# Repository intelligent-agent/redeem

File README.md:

```
     _/_/_/                    _/                                     
    _/    _/    _/_/      _/_/_/    _/_/      _/_/    _/_/_/  _/_/    
   _/_/_/    _/_/_/_/  _/    _/  _/_/_/_/  _/_/_/_/  _/    _/    _/   
  _/    _/  _/        _/    _/  _/        _/        _/    _/    _/    
 _/    _/    _/_/_/    _/_/_/    _/_/_/    _/_/_/  _/    _/    _/     
```

Replicape is an attachment for BeagleBone to control control 3D printers and CNC machines, such as routers, lathes and mills.

Redeem is its firmware; it accepts g-codes and translates them into coordinates for your device.

## Software features

- Acceleration with corner speed prediction
- Printer settings loaded from files
- Controllable via OctoPrint, ethernet, USB or MagnaScreen
- Written in python for extensibility
- Optimized for BeagleBone's secondary processing units
- Extendable plugin architecture

## Documentation

[http://wiki.thing-printer.com/](Intelligent-Agent Wiki)

## Installation options

### BeagleBone image

Umikaze (based on Ubuntu 18.04.2 LTS)

### Source install

**WARNING**: The current `master` branch is considered stable, though not yet released while we integrate a few more features to release 2.2.1.
As such, please note that as of this latest change to the master branch, you should be building Redeem off a platform similar to that built by the [https://github.com/intelligent-agent/Umikaze](Umikaze) 
[https://github.com/intelligent-agent/Umikaze/blob/master/Packages/install_redeem](Redeem build script).

The build script will not run as a standalone, however it does include all dependency installations and virtual environment setup, as well as inclusion of the systemd service integration.

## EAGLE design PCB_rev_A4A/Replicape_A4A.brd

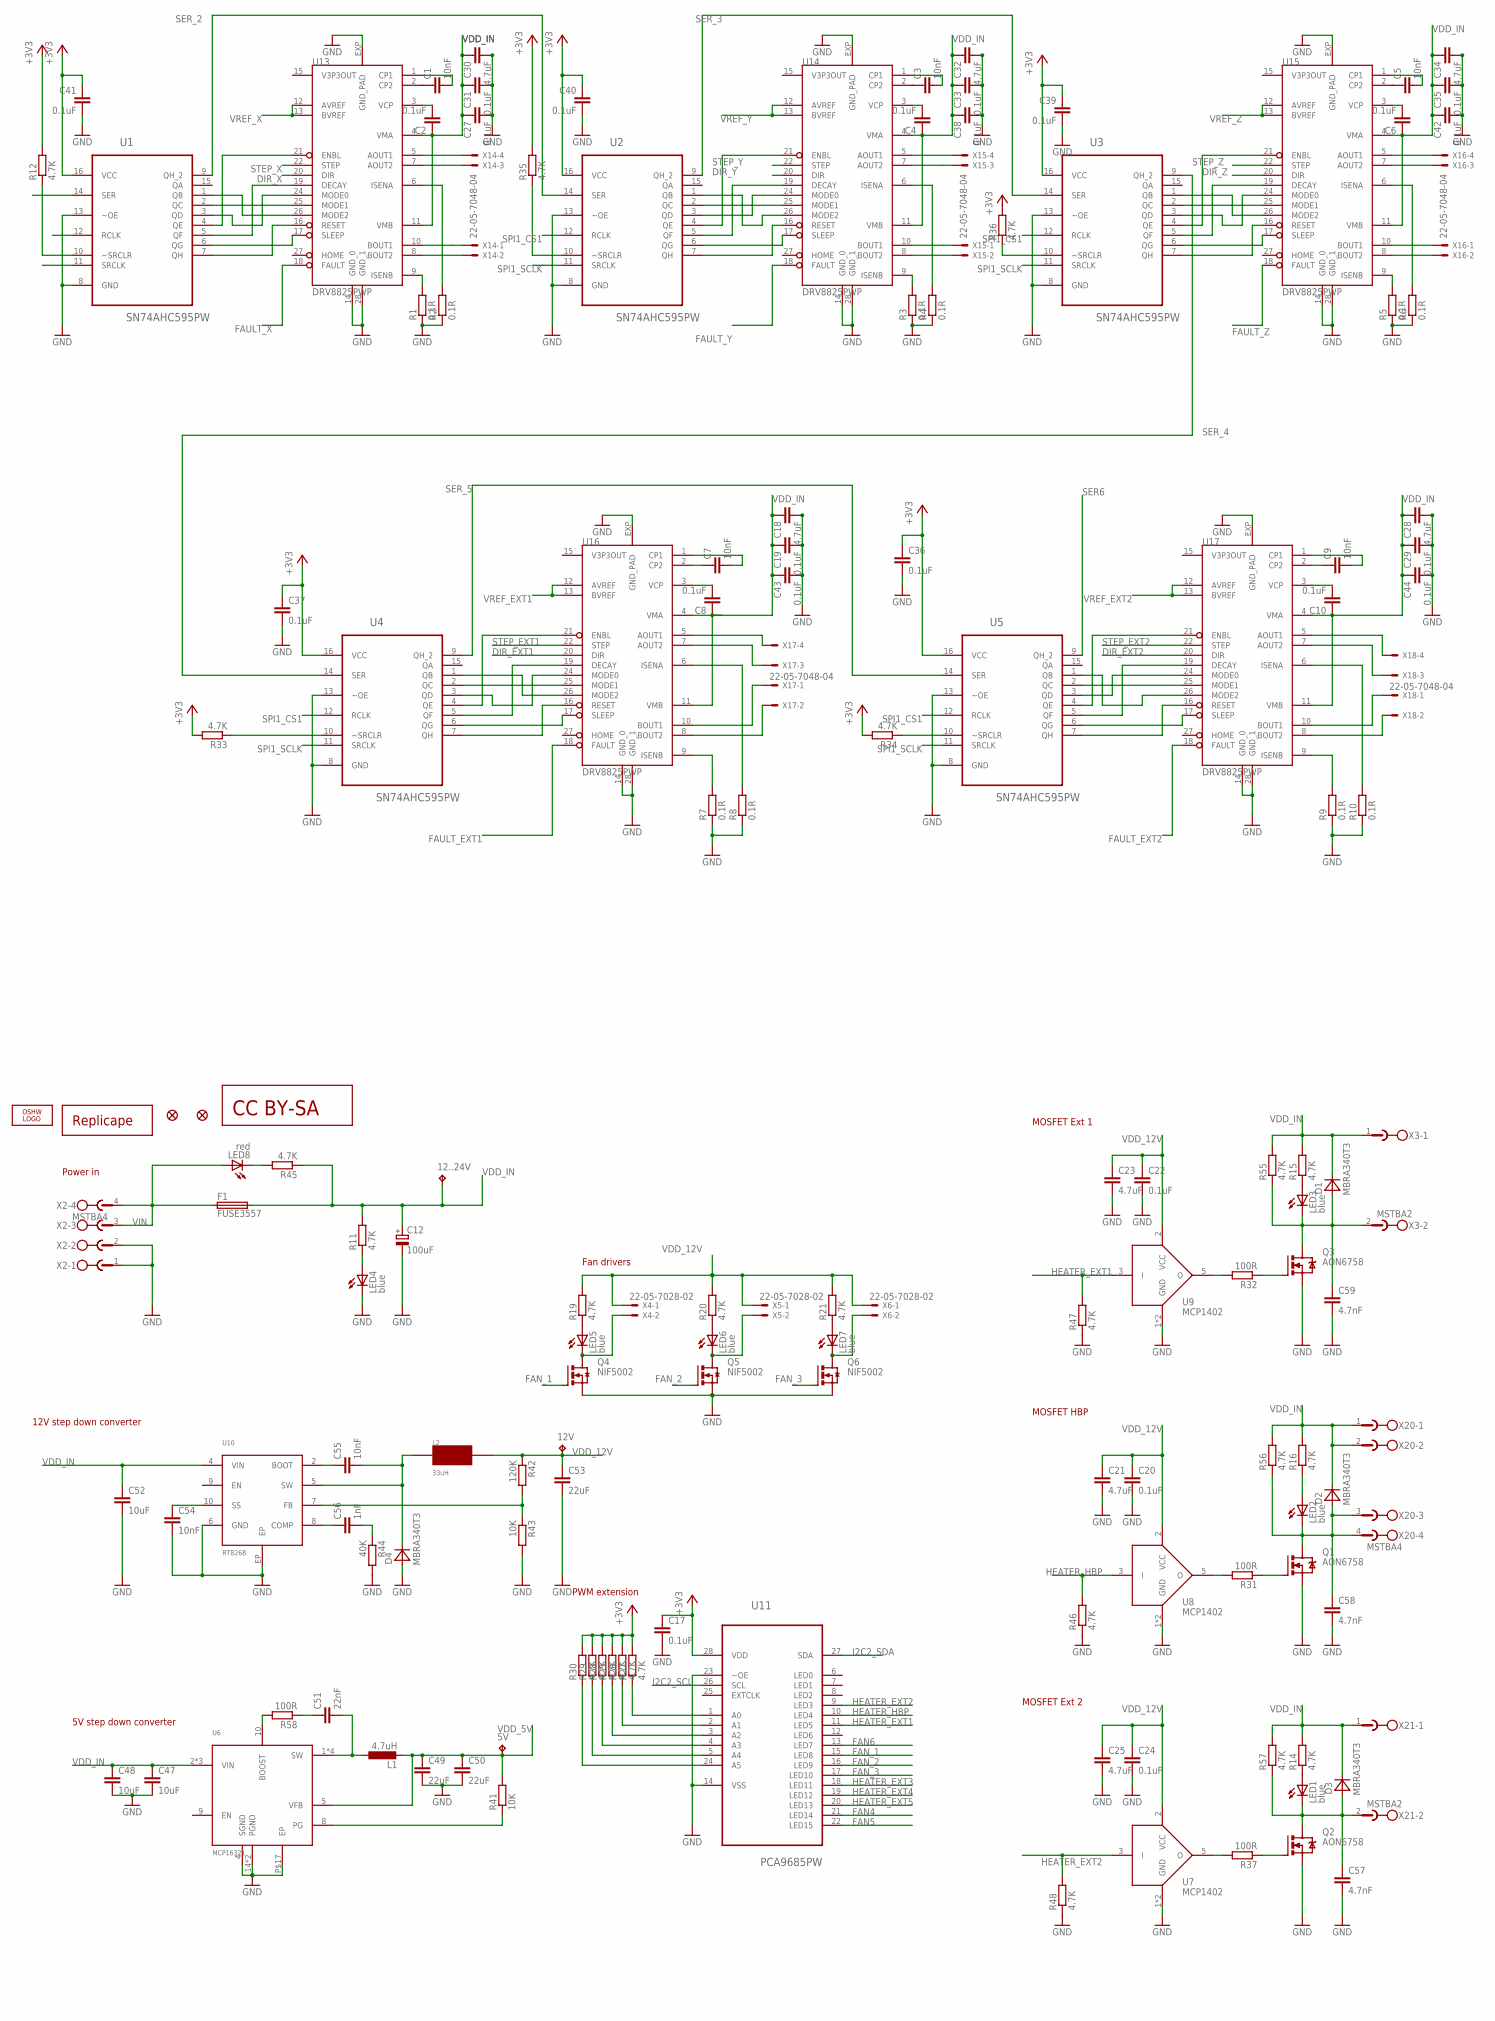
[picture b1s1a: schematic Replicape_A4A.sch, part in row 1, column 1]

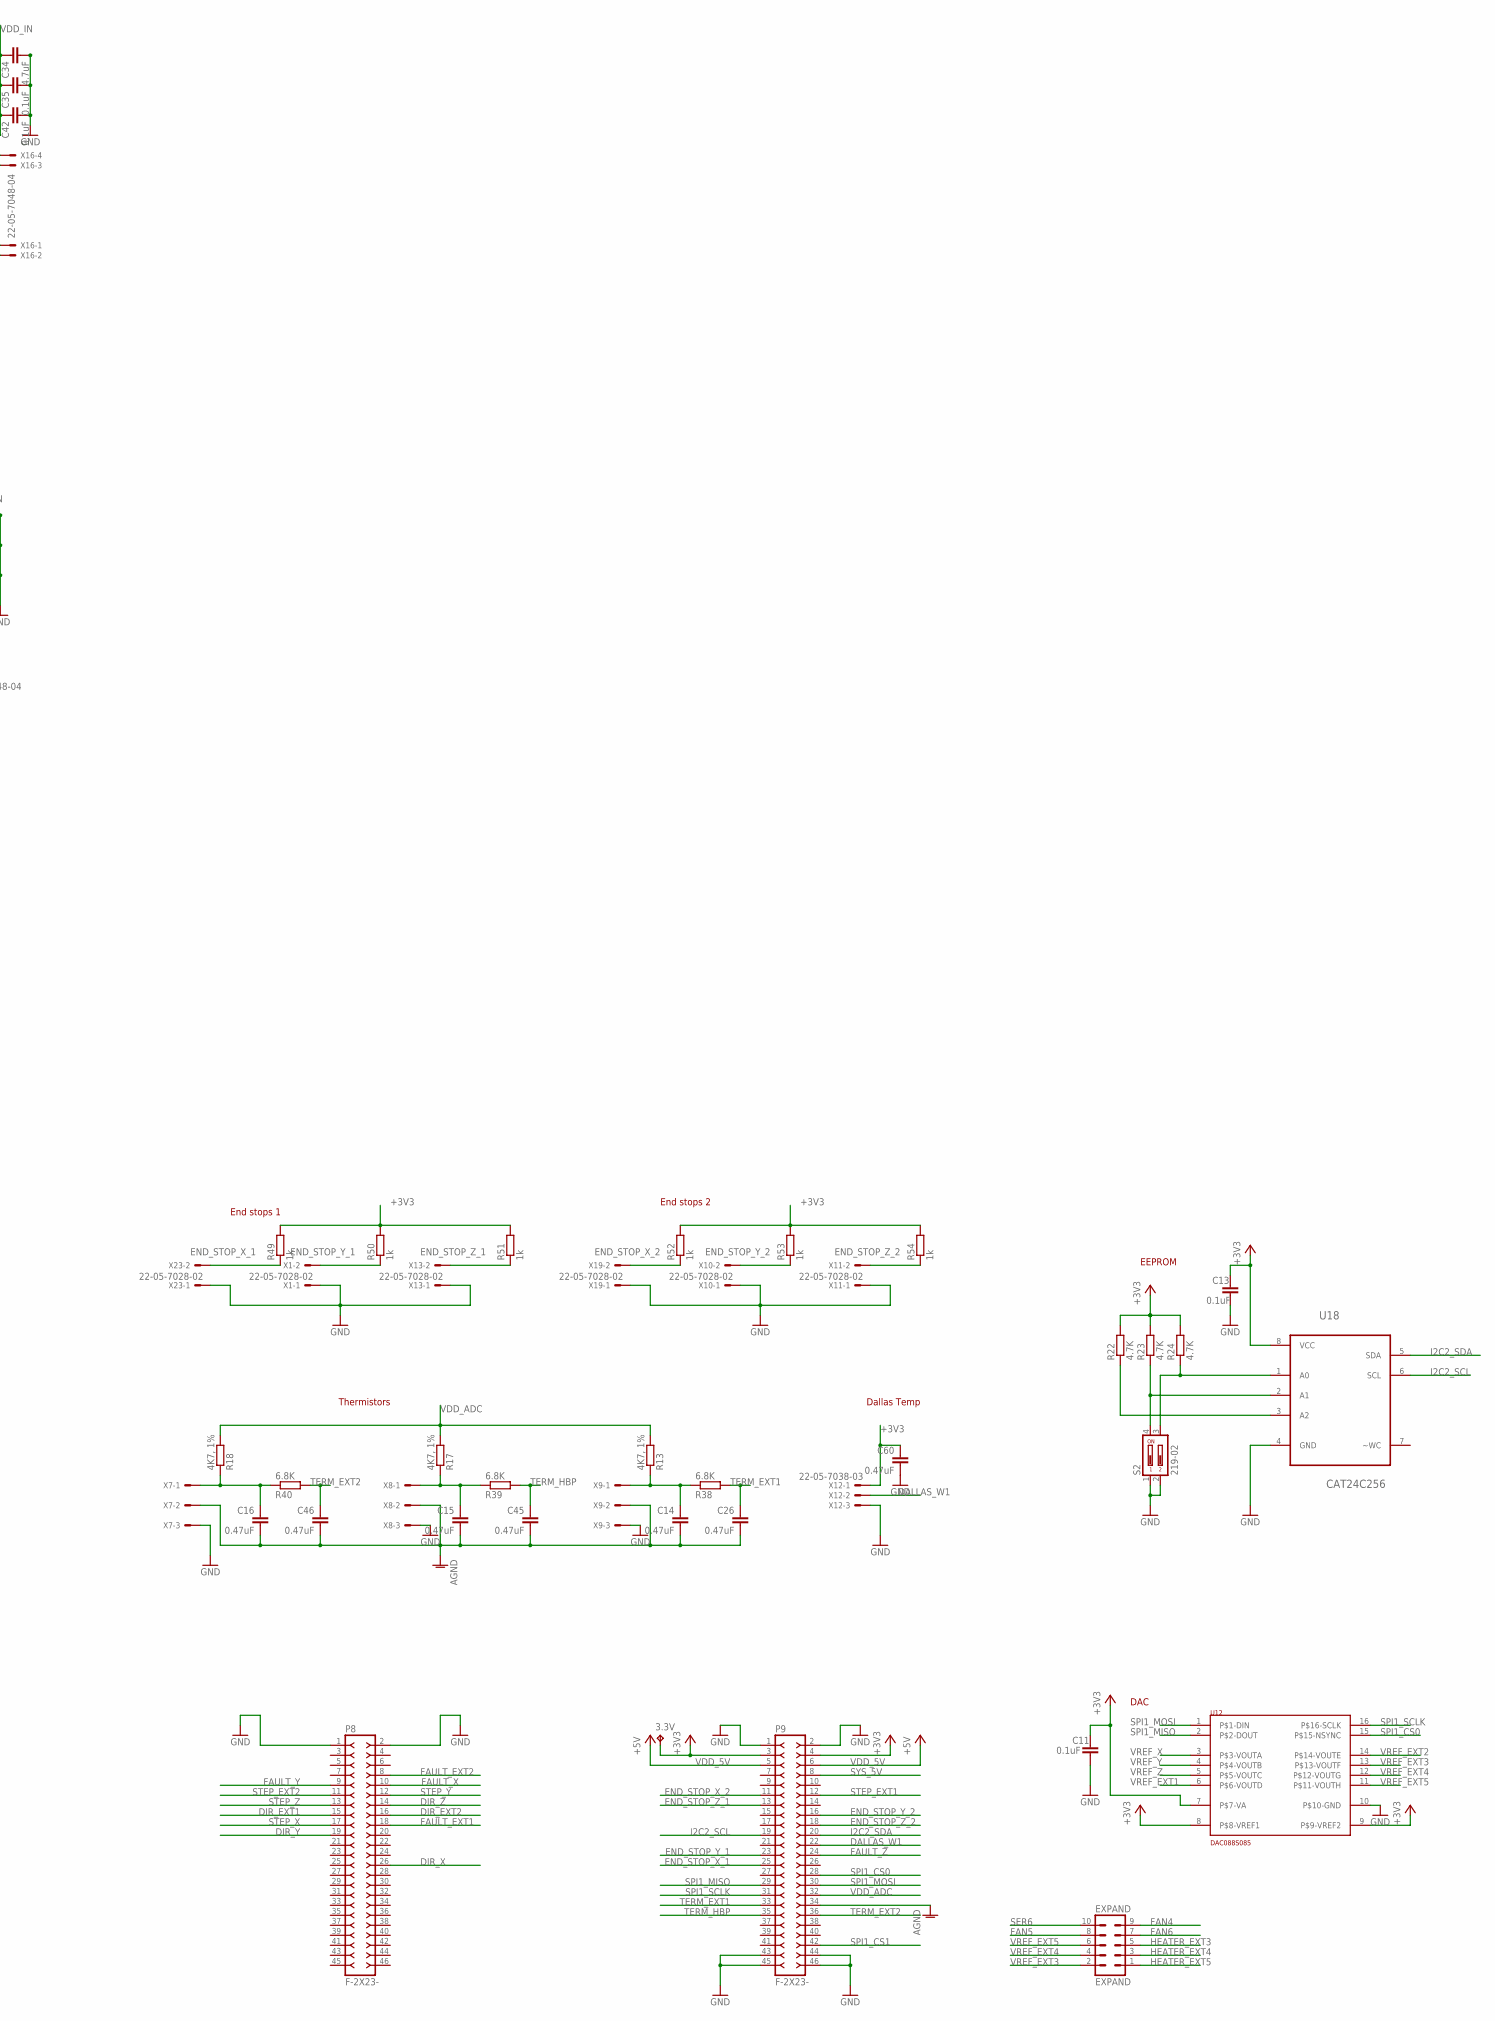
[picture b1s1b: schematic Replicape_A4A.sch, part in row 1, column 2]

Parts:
3.3V, 5V, 12..24V, 12V: TPB1,27; B1,27
C1, C3, C5, C7, C9, C54, C55: 10nF; C0402
C2, C4, C6, C8, C10, C11, C13, C17, C19, C20, C22, C24, C27, C29, C31, C33, C35, C36, C37, C38, C39, C40, C41, C42, C43, C44: 0.1uF; C0402
C12: 100uF; 140CLH-0810
C14, C15, C16, C26, C45, C46, C60: 0.47uF; C0402
C18, C28, C30, C32, C34: 4.7uF; C0603
C21, C23, C25: 4.7uF; C0402
C47, C48, C52: 10uF; C1206
C49, C50, C53: 22uF; C0805
C51: 22nF; C0402
C56: 1nF; C0402
C57, C58, C59: 4.7nF; C0402
D1, D2, D3, D4: MBRA340T3; SMA
EXPAND: EXPAND; MA05-2
F1: FUSE3557; 3557
JP1, JP2: FIDUCIAL1X2.5; FIDUCIAL-1X2.5
L1: 4.7uH; VLC5020
L2: 33uH; NR8040T330
LED1, LED2, LED3, LED4, LED5, LED6, LED7: blue; CHIP-LED0603
LED8: red; CHIP-LED0603
LOGO1: OSHW_LOGO_FILLX0200-NT; OSHW_FILLX200_NOTEXT
P8, P9: F-2X23-; DIL-100-2X23
Q1, Q2, Q3: AON6758; 8-DFN-EP-(5X6)
Q4, Q5, Q6: NIF5002; SOT223
R1, R2, R3, R4, R5, R6, R7, R8, R9, R10: 0.1R; R0805
R11, R12, R14, R15, R16, R19, R20, R21, R22, R23, R24, R25, R26, R27, R28, R29, R30, R33, R34, R35, R36, R45, R46, R47, R48, R55, R56, R57: 4.7K; R0402
R13, R17, R18: 4K7, 1%; R0402
R31, R32, R37, R58: 100R; R0402
R38, R39, R40: 6.8K; R0402
R41, R43: 10K; R0402
R42: 120K; R0402
R44: 40K; R0402
R49, R50, R51, R52, R53, R54: 1k; R0402
S2: 219-02; CTS-219-02
U1, U2, U3, U4, U5: SN74AHC595PW; SOP65P640X120-16N
U6: MCP16321; QFN-16
U7, U8, U9: MCP1402; SOT23-5L
U10: RT8268; MSOP10
U11: PCA9685PW; SOP65P640X110-28N
U12: DAC088S085; TSSOP-16
U13, U14, U15, U16, U17: DRV8825PWP; TSSOP-28
U18: CAT24C256; SOIC127P600X175-8N
U$2: REPLICAPE-LOGO
U$3: CC-BY-SA
X1, X4, X5, X6, X10, X11, X13, X19, X23: 22-05-7028-02; 7395-02
X2, X20: MSTBA4
X3, X21: MSTBA2
X7, X8, X9, X12: 22-05-7038-03; 7395-03
X14, X15, X16, X17, X18: 22-05-7048-04; 7395-04

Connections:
+3V3: 3.3V.TP, C11.1, C13.1, C17.1, C36.1, C37.1, C39.1, C40.1, C41.1, C60.1, P9.3, P9.4, R12.2, R22.2, R23.2, R24.2, R25.2, R26.2, R27.2, R28.2, R29.2, R30.2, R33.2, R34.2, R35.2, R36.2, R49.2, R50.2, R51.2, R52.2, R53.2, R54.2, U1.16 (VCC), U2.16 (VCC), U3.16 (VCC), U4.16 (VCC), U5.16 (VCC), U11.28 (VDD), U12.7 (P$7-VA), U12.8 (P$8-VREF1), U12.9 (P$9-VREF2), U18.8 (VCC), X12.1
A1_X: U13.5 (AOUT1), X14.4
A2_X: U13.7 (AOUT2), X14.3
AGND: C14.2, C15.2, C16.2, C26.2, C45.2, C46.2, P9.34, X7.2, X8.2, X9.2
B1_X: U13.10 (BOUT1), X14.1
DALLAS_W1: P9.22, X12.2
DIR_EXT1: P8.15, U16.20 (DIR)
DIR_EXT2: P8.16, U17.20 (DIR)
DIR_X: P8.26, U13.20 (DIR)
DIR_Y: P8.19, U14.20 (DIR)
DIR_Z: P8.14, U15.20 (DIR)
END_STOP_X_1: P9.25, R49.1, X23.2
END_STOP_X_2: P9.11, R52.1, X19.2
END_STOP_Y_1: P9.23, R50.1, X1.2
END_STOP_Y_2: P9.16, R53.1, X10.2
END_STOP_Z_1: P9.13, R51.1, X13.2
END_STOP_Z_2: P9.18, R54.1, X11.2
EXT1_DECAY: U4.5 (QF), U16.19 (DECAY)
EXT1_MODE0: U4.3 (QD), U16.24 (MODE0)
EXT1_MODE1: U4.2 (QC), U16.25 (MODE1)
EXT1_MODE2: U4.1 (QB), U16.26 (MODE2)
EXT1_NENABLE: U4.4 (QE), U16.21 (ENBL)
EXT1_NRESET: U4.7 (QH), U16.16 (RESET)
EXT1_NSLEEP: U4.6 (QG), U16.17 (SLEEP)
EXT2_DECAY: U5.5 (QF), U17.19 (DECAY)
EXT2_MODE0: U5.3 (QD), U17.24 (MODE0)
EXT2_MODE1: U5.2 (QC), U17.25 (MODE1)
EXT2_MODE2: U5.1 (QB), U17.26 (MODE2)
EXT2_NENABLE: U5.4 (QE), U17.21 (ENBL)
EXT2_NRESET: U5.7 (QH), U17.16 (RESET)
EXT2_NSLEEP: U5.6 (QG), U17.17 (SLEEP)
FAN4: EXPAND.9, U11.21 (LED14)
FAN5: EXPAND.8, U11.22 (LED15)
FAN6: EXPAND.7, U11.13 (LED7)
FAN_1: Q4.1 (G), U11.15 (LED8)
FAN_2: Q5.1 (G), U11.16 (LED9)
FAN_3: Q6.1 (G), U11.17 (LED10)
FAULT_EXT1: P8.18, U16.18 (FAULT)
FAULT_EXT2: P8.8, U17.18 (FAULT)
FAULT_X: P8.10, U13.18 (FAULT)
FAULT_Y: P8.9, U14.18 (FAULT)
FAULT_Z: P9.24, U15.18 (FAULT)
GND: C11.2, C12.-, C13.2, C17.2, C18.2, C19.2, C20.2, C21.2, C22.2, C23.2, C24.2, C25.2, C27.2, C28.2, C29.2, C30.2, C31.2, C32.2, C33.2, C34.2, C35.2, C36.2, C37.2, C38.2, C39.2, C40.2, C41.2, C42.2, C43.2, C44.2, C47.2, C48.2, C49.2, C50.2, C52.2, C53.2, C54.2, C57.2, C58.2, C59.2, C60.2, D4.A, LED4.C, P8.1, P8.2, P9.1, P9.2, P9.43, P9.44, P9.45, P9.46, Q1.1 (S), Q1.2 (S), Q1.3 (S), Q2.1 (S), Q2.2 (S), Q2.3 (S), Q3.1 (S), Q3.2 (S), Q3.3 (S), Q4.3 (S), Q5.3 (S), Q6.3 (S), R1.1, R2.1, R3.1, R4.1, R5.1, R6.1, R7.1, R8.1, R9.1, R10.1, R43.2, R44.2, R46.1, R47.1, R48.1, S2.1, S2.2, U1.8 (GND), U1.13 (~OE), U2.8 (GND), U2.13 (~OE), U3.8 (GND), U3.13 (~OE), U4.8 (GND), U4.13 (~OE), U5.8 (GND), U5.13 (~OE), U6.4 (SGND), U6.14 (PGND), U6.15 (PGND), U6.P$17 (EP), U7.1 (GND), U7.4 (GND), U8.1 (GND), U8.4 (GND), U9.1 (GND), U9.4 (GND), U10.6 (GND), U10.EP, U11.14 (VSS), U11.23 (~OE), U12.10 (P$10-GND), U13.14 (GND_0), U13.28 (GND_1), U13.EXP (GND_PAD), U14.14 (GND_0), U14.28 (GND_1), U14.EXP (GND_PAD), U15.14 (GND_0), U15.28 (GND_1), U15.EXP (GND_PAD), U16.14 (GND_0), U16.28 (GND_1), U16.EXP (GND_PAD), U17.14 (GND_0), U17.28 (GND_1), U17.EXP (GND_PAD), U18.4 (GND), X1.1, X2.1, X2.2, X7.3, X8.3, X9.3, X10.1, X11.1, X12.3, X13.1, X19.1, X23.1
HEATER_EXT1: R47.2, U9.3 (I), U11.11 (LED5)
HEATER_EXT2: R48.2, U7.3 (I), U11.9 (LED3)
HEATER_EXT3: EXPAND.5, U11.18 (LED11)
HEATER_EXT4: EXPAND.3, U11.19 (LED12)
HEATER_EXT5: EXPAND.1, U11.20 (LED13)
HEATER_HBP: R46.2, U8.3 (I), U11.10 (LED4)
I2C2_SCL: P9.19, U11.26 (SCL), U18.6 (SCL)
I2C2_SDA: P9.20, U11.27 (SDA), U18.5 (SDA)
unnamed: C51.1, R58.1
unnamed: U13.8 (BOUT2), X14.2
unnamed: U14.8 (BOUT2), X15.2
unnamed: U15.10 (BOUT1), X16.1
unnamed: U15.8 (BOUT2), X16.2
unnamed: LED8.C, R45.2
unnamed: LED5.A, R19.1
unnamed: C1.1, U13.2 (CP2)
unnamed: C1.2, U13.1 (CP1)
unnamed: R1.2, U13.9 (ISENB)
unnamed: R2.2, U13.6 (ISENA)
unnamed: R32.2, U9.5 (O)
unnamed: C2.2, U13.3 (VCP)
unnamed: Q2.4 (G), R37.1
unnamed: C3.1, U14.2 (CP2)
unnamed: C3.2, U14.1 (CP1)
unnamed: R3.2, U14.9 (ISENB)
unnamed: R4.2, U14.6 (ISENA)
unnamed: C4.2, U14.3 (VCP)
unnamed: R37.2, U7.5 (O)
unnamed: C5.1, U15.2 (CP2)
unnamed: C5.2, U15.1 (CP1)
unnamed: R5.2, U15.9 (ISENB)
unnamed: R6.2, U15.6 (ISENA)
unnamed: C6.2, U15.3 (VCP)
unnamed: R27.1, U11.1 (A0)
unnamed: R26.1, U11.2 (A1)
unnamed: Q1.4 (G), R31.1
unnamed: R31.2, U8.5 (O)
unnamed: C57.1, D3.A, LED1.C, Q2.5 (D), Q2.6 (D), Q2.7 (D), Q2.8 (D), Q2.TH (D), R57.1, X21.2
unnamed: C7.1, U16.2 (CP2)
unnamed: C7.2, U16.1 (CP1)
unnamed: R7.2, U16.9 (ISENB)
unnamed: R8.2, U16.6 (ISENA)
unnamed: C8.2, U16.3 (VCP)
unnamed: R25.1, U11.3 (A2)
unnamed: C9.1, U17.2 (CP2)
unnamed: C9.2, U17.1 (CP1)
unnamed: R9.2, U17.9 (ISENB)
unnamed: R10.2, U17.6 (ISENA)
unnamed: C10.2, U17.3 (VCP)
unnamed: R28.1, U11.4 (A3)
unnamed: R29.1, U11.5 (A4)
unnamed: LED4.A, R11.1
unnamed: R12.1, U1.10 (~SRCLR)
unnamed: R33.1, U4.10 (~SRCLR)
unnamed: R34.1, U5.10 (~SRCLR)
unnamed: R35.1, U2.10 (~SRCLR)
unnamed: R36.1, U3.10 (~SRCLR)
unnamed: R30.1, U11.24 (A5)
unnamed: LED7.C, Q6.2 (D), Q6.4 (D), X6.2
unnamed: LED6.C, Q5.2 (D), Q5.4 (D), X5.2
unnamed: LED5.C, Q4.2 (D), Q4.4 (D), X4.2
unnamed: LED6.A, R20.1
unnamed: LED7.A, R21.1
unnamed: LED3.A, R15.1
unnamed: R58.2, U6.10 (BOOST)
unnamed: LED1.A, R14.1
unnamed: LED2.A, R16.1
unnamed: Q3.4 (G), R32.1
unnamed: R24.1, S2.3, U18.1 (A0)
unnamed: R23.1, S2.4, U18.2 (A1)
unnamed: R22.1, U18.3 (A2)
unnamed: R42.2, R43.1, U10.7 (FB)
unnamed: C59.1, D1.A, LED3.C, Q3.5 (D), Q3.6 (D), Q3.7 (D), Q3.8 (D), Q3.TH (D), R55.1, X3.2
unnamed: C14.1, R13.1, R38.1, X9.1
unnamed: C55.2, D4.C, L2.P$2, U10.5 (SW)
unnamed: R41.1, U6.8 (PG)
unnamed: C16.1, R18.1, R40.1, X7.1
unnamed: C15.1, R17.1, R39.1, X8.1
unnamed: C58.1, D2.A, LED2.C, Q1.5 (D), Q1.6 (D), Q1.7 (D), Q1.8 (D), Q1.TH (D), R56.1, X20.3, X20.4
unnamed: C54.1, U10.10 (SS)
unnamed: C56.1, U10.8 (COMP)
unnamed: C55.1, U10.2 (BOOT)
unnamed: C56.2, R44.1
SER6: EXPAND.10, U5.9 (QH_2)
SER_2: U1.9 (QH_2), U2.14 (SER)
SER_3: U2.9 (QH_2), U3.14 (SER)
SER_4: U3.9 (QH_2), U4.14 (SER)
SER_5: U4.9 (QH_2), U5.14 (SER)
SPI1_CS0: P9.28, U12.15 (P$15-NSYNC)
SPI1_CS1: P9.42, U1.12 (RCLK), U2.12 (RCLK), U3.12 (RCLK), U4.12 (RCLK), U5.12 (RCLK)
SPI1_MISO: P9.29, U12.2 (P$2-DOUT)
SPI1_MOSI: P9.30, U1.14 (SER), U12.1 (P$1-DIN)
SPI1_SCLK: P9.31, U1.11 (SRCLK), U2.11 (SRCLK), U3.11 (SRCLK), U4.11 (SRCLK), U5.11 (SRCLK), U12.16 (P$16-SCLK)
STEP1_EXT1: U16.5 (AOUT1), X17.4
STEP1_EXT2: U17.5 (AOUT1), X18.4
STEP1_Y: U14.5 (AOUT1), X15.4
STEP1_Z: U15.5 (AOUT1), X16.4
STEP2_EXT1: U16.7 (AOUT2), X17.3
STEP2_EXT2: U17.7 (AOUT2), X18.3
STEP2_Y: U14.7 (AOUT2), X15.3
STEP2_Z: U15.7 (AOUT2), X16.3
STEP3_EXT1: U16.10 (BOUT1), X17.1
STEP3_EXT2: U17.10 (BOUT1), X18.1
STEP3_Y: U14.10 (BOUT1), X15.1
STEP4_EXT1: U16.8 (BOUT2), X17.2
STEP4_EXT2: U17.8 (BOUT2), X18.2
STEP_EXT1: P9.12, U16.22 (STEP)
STEP_EXT2: P8.11, U17.22 (STEP)
STEP_X: P8.17, U13.22 (STEP)
STEP_Y: P8.12, U14.22 (STEP)
STEP_Z: P8.13, U15.22 (STEP)
SW: C51.2, L1.1, U6.1 (SW), U6.12 (SW), U6.13 (SW), U6.16 (SW)
SYS_5V: P9.8
TERM_EXT1: C26.1, P9.33, R38.2
TERM_EXT2: C46.1, P9.36, R40.2
TERM_HBP: C45.1, P9.35, R39.2
VDD_5V: 5V.TP, C49.1, C50.1, L1.2, P9.5, P9.6, R41.2, U6.5 (VFB)
VDD_12V: 12V.TP, C20.1, C21.1, C22.1, C23.1, C24.1, C25.1, C53.1, L2.P$1, R19.2, R20.2, R21.2, R42.1, U7.2 (VCC), U8.2 (VCC), U9.2 (VCC), X4.1, X5.1, X6.1
VDD_ADC: P9.32, R13.2, R17.2, R18.2
VDD_IN: 12..24V.TP, C2.1, C4.1, C6.1, C8.1, C10.1, C12.+, C18.1, C19.1, C27.1, C28.1, C29.1, C30.1, C31.1, C32.1, C33.1, C34.1, C35.1, C38.1, C42.1, C43.1, C44.1, C47.1, C48.1, C52.1, D1.C, D2.C, D3.C, F1.3 (2), F1.4 (2), R11.2, R14.2, R15.2, R16.2, R45.1, R55.2, R56.2, R57.2, U6.2 (VIN), U6.3 (VIN), U6.11 (VIN), U10.4 (VIN), U13.4 (VMA), U13.11 (VMB), U14.4 (VMA), U14.11 (VMB), U15.4 (VMA), U15.11 (VMB), U16.4 (VMA), U16.11 (VMB), U17.4 (VMA), U17.11 (VMB), X3.1, X20.1, X20.2, X21.1
VIN: F1.1, F1.2 (1), LED8.A, X2.3, X2.4
VREF_EXT1: U12.6 (P$6-VOUTD), U16.12 (AVREF), U16.13 (BVREF)
VREF_EXT2: U12.14 (P$14-VOUTE), U17.12 (AVREF), U17.13 (BVREF)
VREF_EXT3: EXPAND.2, U12.13 (P$13-VOUTF)
VREF_EXT4: EXPAND.4, U12.12 (P$12-VOUTG)
VREF_EXT5: EXPAND.6, U12.11 (P$11-VOUTH)
VREF_X: U12.3 (P$3-VOUTA), U13.12 (AVREF), U13.13 (BVREF)
VREF_Y: U12.4 (P$4-VOUTB), U14.12 (AVREF), U14.13 (BVREF)
VREF_Z: U12.5 (P$5-VOUTC), U15.12 (AVREF), U15.13 (BVREF)
X_DECAY: U1.5 (QF), U13.19 (DECAY)
X_MODE0: U1.3 (QD), U13.24 (MODE0)
X_MODE1: U1.2 (QC), U13.25 (MODE1)
X_MODE2: U1.1 (QB), U13.26 (MODE2)
X_NENABLE: U1.4 (QE), U13.21 (ENBL)
X_NRESET: U1.7 (QH), U13.16 (RESET)
X_NSLEEP: U1.6 (QG), U13.17 (SLEEP)
Y_DECAY: U2.5 (QF), U14.19 (DECAY)
Y_MODE0: U2.3 (QD), U14.24 (MODE0)
Y_MODE1: U2.2 (QC), U14.25 (MODE1)
Y_MODE2: U2.1 (QB), U14.26 (MODE2)
Y_NENABLE: U2.4 (QE), U14.21 (ENBL)
Y_NRESET: U2.7 (QH), U14.16 (RESET)
Y_NSLEEP: U2.6 (QG), U14.17 (SLEEP)
Z_DECAY: U3.5 (QF), U15.19 (DECAY)
Z_MODE0: U3.3 (QD), U15.24 (MODE0)
Z_MODE1: U3.2 (QC), U15.25 (MODE1)
Z_MODE2: U3.1 (QB), U15.26 (MODE2)
Z_NENABLE: U3.4 (QE), U15.21 (ENBL)
Z_NRESET: U3.7 (QH), U15.16 (RESET)
Z_NSLEEP: U3.6 (QG), U15.17 (SLEEP)

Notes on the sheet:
Fan drivers
PWM extension
Power in
5V step down converter
12V step down converter
MOSFET Ext 1
MOSFET HBP
MOSFET Ext 2
End stops 2
Thermistors
End stops 1
Dallas Temp
EEPROM
DAC

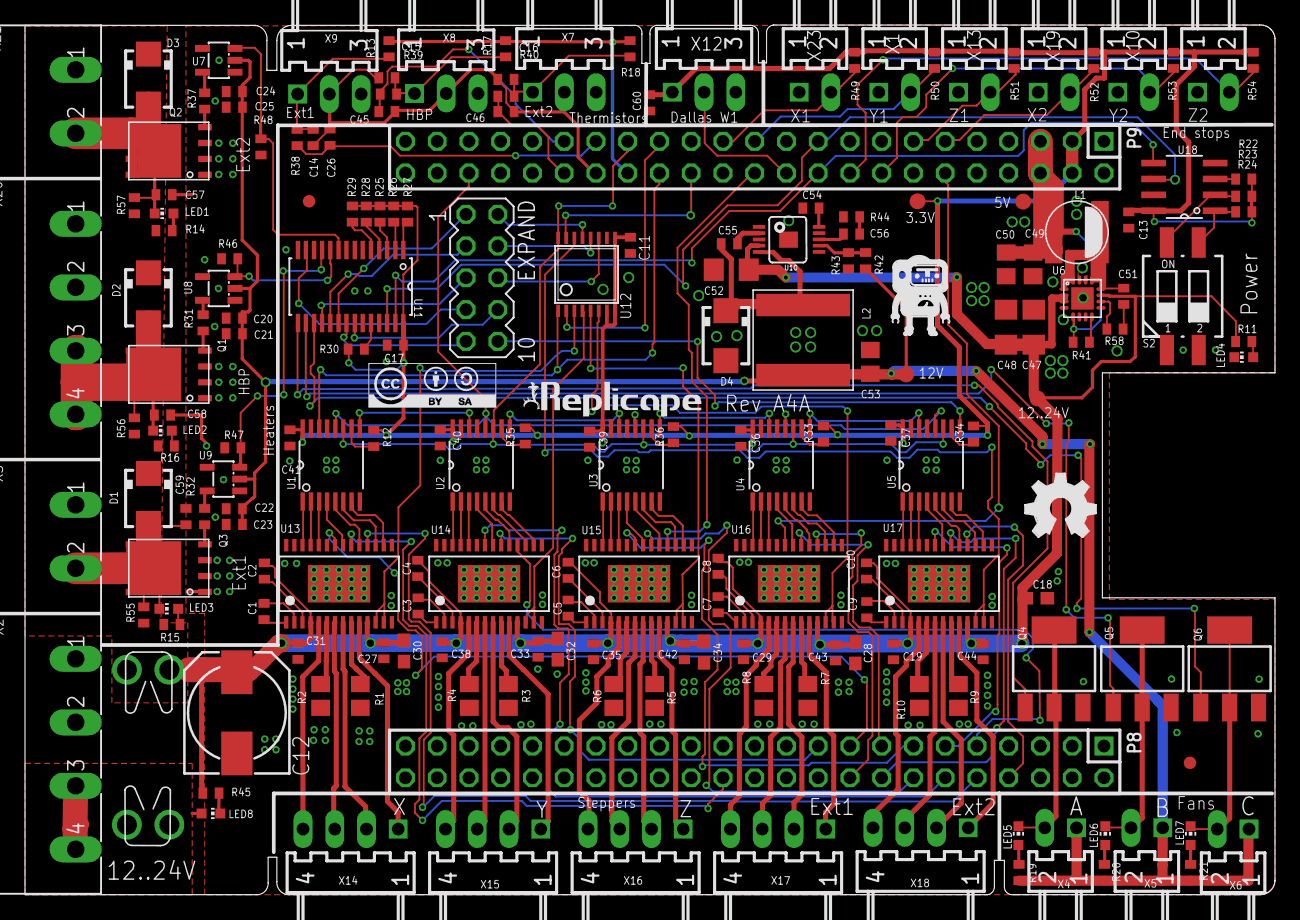
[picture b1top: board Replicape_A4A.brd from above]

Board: 2 copper layers, 100.0 x 69.6 mm, 193 parts (0 on the bottom side), 192 nets.

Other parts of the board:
U$1: LOGO_BIG

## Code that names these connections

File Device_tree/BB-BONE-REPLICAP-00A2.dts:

/*
 * Copyright (C) 2013 Intelligent Agent AS	<elias@iagent.no>
 *
 * This program is free software; you can redistribute it and/or modify
 * it under the terms of the GNU General Public License version 2 as
 * published by the Free Software Foundation.
 */
/dts-v1/;
/plugin/;

/ {
	compatible = "ti,beaglebone", "ti,beaglebone-black";

	/* identification */
	part-number = "BB-BONE-REPLICAP";
	version = "00A2";

	/* state the resources this cape uses */
	exclusive-use =
		/* the pin header P8 uses */
		"P8.16", /* (3) DIR_EXT_2 	*/
		"P8.15", /* (4) DIR_EXT_1 	*/
		"P8.14", /* (5) DIR_Z 		*/
		"P8.17", /* (6) STEP_X 		*/
		"P8.7",  /* END_STOP_Y1 */
		"P8.8",  /* FAULT_EXT_2	*/
		"P8.9",  /* FAULT_Y 	*/
		"P8.10", /* FAULT_x 	*/
		"P8.18", /* FAULT_EXT_1	*/
		"P8.11", /* (22) STEP_EXT_2	*/
		"P8.12", /* (23) STEP_Y		*/
		"P8.13", /* (24) STEP_Z		*/
		"P8.19", /* (25) DIR_Y		*/
		"P8.26", /* DIR_X		*/
		/* the pin header P9 uses */
		"P9.11", /* END_STOP_Z1	*/
		"P9.12", /* STEP_EXT_1	*/
		"P9.13", /* END_STOP_X2	*/
		"P9.18", /* END_STOP_Z2	*/
		"P9.24", /* FAULT_Z		*/
		"P9.25", /* END_STOP_Y2	*/
		"P9.26", /* END_STOP_X1	*/
		"P9.28", /* SPI1_CS0 	*/
		"P9.29", /* SPI1_MISO   */
		"P9.30", /* SPI1_MOSI	*/
		"P9.31", /* SPI1_SCLK	*/
		"P9.33", /* AIN4		*/
		"P9.35", /* AIN6		*/
		"P9.36", /* AIN5		*/
		"P9.42", /* SPI1_CS1	*/
		/* Hardware IP cores in use */
		"spi1", 
		"pruss"; 

	fragment@0 {
		target = <&am33xx_pinmux>;
		__overlay__ {
			bone_replicape_spi1_pins: pinmux_replicape_spi1_pins {
				pinctrl-single,pins = <
					0x190 0x13	/* P9_31 = mcasp0_aclkx.spi1_sclk				 , OUTPUT_PULLUP | MODE3 */
					0x194 0x33	/* P9_29 = mcasp0_fsx.spi1_d0					 , INPUT_PULLUP  | MODE3 */
					0x198 0x13	/* P9_30 = mcasp0_axr0.spi1_d1					 , OUTPUT_PULLUP | MODE3 */
					0x19c 0x13	/* P9_28 = mcasp0_ahclkr.spi1_cs0				 , OUTPUT_PULLUP | MODE3 */					
					0x164 0x12  /* P9_42 = GPIO0_7 =  eCAP0_in_PWM0_out.gpio0[7] , OUTPUT_PULLUP | MODE2 */
				>;
			};					
			pruicss_stepper_pins: pinmux_pruicss_stepper_pins{
				pinctrl-single,pins = <
					0x038 0x07 // P8_16 (3)  = DIR_EXT_2	= GPIO1_14
					0x03C 0x07 // P8_15 (4)  = DIR_EXT_1	= GPIO1_15
					0x028 0x07 // P8_14 (5)  = DIR_Z   	 	= GPIO0_26
					0x02C 0x07 // P8_17 (6)  = STEP_X 	 	= GPIO0_27
				 	0x034 0x07 // P8_11 (22) = step_ext_2 	= GPIO1_13	
					0x030 0x07 // P8_12 (23) = Step_y	 	= GPIO1_12
					0x024 0x07 // P8_13 (24) = Step_z	 	= GPIO0_23
					0x020 0x07 // P8_19 (25) = Dir_y 	 	= GPIO0_22
					0x07C 0x07 // P8_26 	 = Dir_x		= GPIO1_29
					0x078 0x07 // P9_12 	 = step ext 1 	= GPIO1_28
				>;
			};		
		
			stepper_fault_pins: pinmux_stepper_fault_pins{
				pinctrl-single,pins = <
					0x094 0x37 // P8_8  = Fault Ext 2 	= GPIO2_2    gpmc_oen_ren.gpio2[3]  
					0x09C 0x37 // P8_9  = FAYLT Y		= GPIO2_5
					0x098 0x37 // P8_10 = FAULT X     	= GPIO2_4    gpmc_wen.gpio2[4]      
					0x08C 0x37 // P8_18 = Fault_ext 1	= GPIO2_1
					0x184 0x37 // P9_24 = Fault Z		= GPIO0_15
				>;
			};

			end_stop_pins: pinmux_end_stop_pins{
				pinctrl-single,pins = <
					0x090 0x37 // P8_7  = End stop X1  = GPIO2_2
					0x070 0x37 // P9_11 = End stop Y1  = GPIO0_30
					0x074 0x37 // P9_13 = End stop Z1  = GPIO0_31
					0x158 0x37 // P9_18 = End stop Z2  = GPIO0_4
					0x1AC 0x37 // P9_25 = End stop Y2  = GPIO3_21
					0x180 0x37 // P9_26 = End stop X2  = GPIO0_14
				>;
			};
		};
	};

	fragment@1 {
		target = <&spi1>;
		__overlay__ {
			#address-cells 	= <1>;
			#size-cells 	= <0>;
			status			= "okay";
			pinctrl-names	= "default";
			pinctrl-0		= <&bone_replicape_spi1_pins>;	
			cs-gpios 		= <&gpio4 17 0>, <&gpio1 7 0>;

			stepper_control{
				#address-cells 	  = <1>;
				#size-cells 	  = <0>;
				compatible 		  = "spidev";
				reg 			  = <0>;
				spi-max-frequency = <16000000>;
			};

			stepper_current{
				#address-cells 	  = <1>;
				#size-cells 	  = <0>;
				compatible 		  = "spidev";
				reg 			  = <1>;
				spi-max-frequency = <16000000>;
			};
		};
	};

	fragment@2{
		target = <&pruss>;
		__overlay__{
			status = "okay";
			pinctrl-names = "default";
			pinctrl-0 	  = <&pruicss_stepper_pins>;

			stepper_x{
				pin-names 	= "Replic:pru-step_x", "Replic:pru-dir_x";		
				gpios 		= <&gpio1 27 0
						 	   &gpio2 29 0>; 
			};			
			stepper_y{
				pin-names 	= "Replic:pru-step_y", "Replic:pru-dir_y";		
				gpios 		=<&gpio2 12 0
						 	  &gpio1 22 0>; 
			};
			stepper_z{
				pin-names 	= "Replic:pru-step_z", "Replic:pru-dir_z";		
				gpios 		= <&gpio1 23 0
						 	   &gpio1 26 0>; 
			};
			stepper_ext_1{
				pin-names 	= "Replic:pru-step_ext_1", "Replic:pru-dir_ext_1";		
				gpios 		= <&gpio2 28 0
						 	   &gpio2 15 0>; 
			};
			stepper_ext_2{
				pin-names 	= "Replic:pru-step_ext_2", "Replic:pru-dir_ext_2";		
				gpios 		= <&gpio2 13 0
						 	   &gpio2 14 0>; 
			};
		};
	};

	fragment@3 {
		target = <&ocp>;
		__overlay__ {			
			#address-cells = <1>;
			#size-cells = <1>;							

			tscadc {
				compatible = "ti,ti-tscadc";
				reg = <0x44e0d000 0x1000>;

				interrupt-parent = <&intc>;	
				interrupts = <16>;
				ti,hwmods = "adc_tsc";
				status = "okay";

				tsc {
					ti,wires = <4>;
				};
				adc {
					ti,adc-channels = <4>;
				};
			};

			thermistors{
				compatible = "bone-iio-helper";
				vsense-name  = "AIN4", "AIN5", "AIN6", "AIN7";
				vsense-scale = <100     100     100     100 >;
				status = "okay";
			};
			gpio_keys {
				compatible = "gpio-keys";
				pinctrl-names = "default";
				pinctrl-0 = <&end_stop_pins>;
				#address-cells = <1>;
				#size-cells = <0>;

				switch_x1 {
					label = "End-stop-X1";
					debounce_interval = <50>;
					linux,code = <1>;
					gpios = <&gpio3 2 0x5>;
					gpio-key,wakeup;
				};				
				switch_x2 {
					label = "End-stop-X2";
					debounce_interval = <50>;
					linux,code = <2>;
					gpios = <&gpio1 14 0x5>;
					gpio-key,wakeup;
				};
				switch_y1 {
					label = "End-stop-Y1";
					debounce_interval = <50>;
					linux,code = <3>;
					gpios = <&gpio1 30 0x5>;
					gpio-key,wakeup;
				};				
				switch_y2 {
					label = "End-stop-Y2";
					debounce_interval = <50>;
					linux,code = <4>;
					gpios = <&gpio4 21 0x5>;
					gpio-key,wakeup;
				};				
				switch_z1 {
					label = "End-stop-Z1";
					debounce_interval = <50>;
					linux,code = <5>;
					gpios = <&gpio1 31 0x5>;
					gpio-key,wakeup;
				};				
				switch_z2 {
					label = "End-stop-Z2";
					debounce_interval = <50>;
					linux,code = <6>;
					gpios = <&gpio1 4 0x5>;
					gpio-key,wakeup;
				};				
				fault_x {
					label = "Fault_X";
					debounce_interval = <50>;
					linux,code = <7>;
					gpios = <&gpio3 4 0x5>;
					gpio-key,wakeup;
				};				
				fault_y {
					label = "Fault_Y";
					debounce_interval = <50>;
					linux,code = <8>;
					gpios = <&gpio3 5 0x5>;
					gpio-key,wakeup;
				};				
				fault_z {
					label = "Fault_Z";
					debounce_interval = <50>;
					linux,code = <9>;
					gpios = <&gpio1 15 0x5>;
					gpio-key,wakeup;
				};				
				fault_ext1 {
					label = "Fault_Ext_1";
					debounce_interval = <50>;
					linux,code = <10>;
					gpios = <&gpio3 1 0x5>;
					gpio-key,wakeup;
				};				
				fault_ext2 {
					label = "Fault_Ext_2";
					debounce_interval = <50>;
					linux,code = <11>;
					gpios = <&gpio3 2 0x5>;
					gpio-key,wakeup;
				};				

			};
		};
	};
};

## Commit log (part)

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2018-03-21 Automatic generation of Version Number
    The version is based on tags in the git tree
    And the relative placement of the HEAD node of the
    checked out tree.
    Use versioneer for automatic version generation
    Have M115 reflect the long version name
2018-03-21 use the Adafruit BBIO library for PWM so we don't break on new kernels
2018-03-29 restartRedeem wasn't stopping the printer movement fast enough. Perhaps now it will.
2018-04-04 Clean up indention and line endings
2018-04-04 The list of Steppers may be an empty string
2018-04-15 Define styling for reformatting
2018-04-15 Spelling corrections
2018-04-18 Revert "initialize stepper GPIOs in case the kernel/overlay didn't"
    This reverts commit 0ca4ef5608472777545722bdeed691ff98a9773c.
2018-04-19 handle slaved axes at the step level rather than the coordinate level
    In theory, slaved axes should be ignored when doing
    distance/speed/acceleration calculations and when calculating probe
    results, but because slaved axes were being handled at the coordinate
    level, they were included. This change removes them and just duplicates
    steps from a master axis to its slaved axes instead. This results in
    simpler code and correct calculations, but it does add the requirement
2018-04-20 Revert PWM
2018-04-27 Create Compatibility with PIP 10
2018-05-05 ••• Cosmetic Changes
2018-05-05 Clean up PathPlanner.py
2018-05-05 Fix for synchronization issues with buffered, async, and octoprint command queues.
2018-06-14 remove Redeem checks for pasm - we use clpru these days
2018-06-14 ignore noncritical signals like SIGHUP
2018-07-24 switch IntVector3 from long longs to ints
    This results in a range of +/- 2147483647 steps, which at 1000 steps
    per mm is a range of +/- 2000 meters. This should be sufficient for 3d
    printing purposes.
2018-07-24 fix forward declarations of Vector types - GCC accepts this but MSVC doesn't
2018-07-24 always represent step-wise locations with 32 bit integers
2018-07-24 add a few explicit casts to quiet compiler warnings when we really do want to cast
2018-07-25 add blocking behaviors to the new path queue
2018-07-26 first pass at simplifying the optimizer
2018-07-27 wire the new path queue into the path planner with a few TODOs
2018-07-29 reimplement sync events and waiting for the path queue to empty
2018-07-29 fix up the GCC build
2018-07-29 shut down the path queue along with the path planner
2018-07-30 correct integer overflow when calling optimizer from the path queue
2018-08-24 DEPRECATE this branch (#119)
2018-08-26 Use Circle CI to enforce styling
2018-08-26 Updated the default python update script working directory. (#118)
2018-08-26 replace the sync event infrastructure with a callback-based approach
2018-08-26 Rewrite of the path planner
2018-08-27 Make endstop more efficient
    Rather than perform a string comparison every time an endstop is triggered, perform the name-to-bit conversion at initialization and simply test the bit.
2018-08-27 Remove references to http://www.xwaves.net
    The site is no longer active.
    Reference removes with the Author’s permission
2018-08-30 Do installation in development mode
2018-09-01 add PathQueueIndex type to eliminate path index arithmetic bugs
2018-09-03 Style Corrections
2018-09-04 rework the junction speed max-speed-jump calculations to be more correct (and faster)
2018-09-04 Revert "Comment path planner assert until it's fixed"
    This reverts commit 230c094ac4df8843ba5db379ad34a0c5b0363e54.
    It's fixed!
2018-09-05 Convert Style Checks to multiple job workflow
2018-09-05 Resolve G29 macro before executing
2018-09-05 “octo” must own the configuration files
    In order to allow OctoPrint to administer them
2018-09-21 ADDED: .nojekyll file to the gh-pages branch
2018-09-30 use https
2018-10-05 Import redeem relative to file rather than cwd
2018-10-06 use https (#135)
    Avoiding mixed content warnings in the browser using https to load resources.
2018-10-07 Add provision to Unconditionally rebuild the firmware
    By doing so, we no longer need to commit the configuration to a file
    just to be able to change the PRU programs
2018-10-07 Add an identifier for the format of the configuration file
2018-10-07 pru_cfg.h depends on stdint.h
2018-10-07 fix tests that relied on PWM and users not being mocked out
2018-10-07 Correct Servo motion and “Sixify”
2018-11-29 Make import references consistent
2018-11-29 mock out Adafruit_BBIO.PWM
2018-11-29 always import gcodes from redeem/gcodes and log an error if they aren't there
2018-12-01 fix tests that called is_buffered on the GCodeProcessor to call assertGcodeProperties instead
2018-12-01 Add Configuration Version Header
2018-12-01 Import GCodeCommand class rather than the module
2018-12-07 FIXED: Formatting using yapf
2018-12-12 Fixed confusing documentation on the M303 G-code
2018-12-17 Allow changes to TargetTemperature while waiting
    This allows the user to alter temperature targets
    without requiring the previous target to be reached
    While the printer is waiting for heaters, M116 is the active gcode. Normally, this is a synchronous action.
    However, M108 is allowed to be performed to allow the command to be aborted.
    This change also allows M104 (Set extruder target temperature) and M140 (Set bed target temperature) to be executed while M116 remains active.
2018-12-17 FIXED: Not modifying the current byte
    Removing the skip of 0 as a byte_position. This fixes an inconsistency in #145.
2018-12-20 Remove dependency on socat/tty0tty by durectly creating and using PTYs
2019-01-04 open separate files to read and write to a pipe
    Python seems to get upset and throw an invalid seek IOError if we
    read and write to the same pipe through the same file object on
    two threads. Go back to opening two objects - one for reading and
    one for writing.
2019-01-06 Removing Future version requirement.
2019-01-08 •••• Spelling
2019-01-08 Discard Key_pin __main__
2019-01-08 Improve M27 response. #142
    Reset SD Manager at end-of-print
2019-01-10 remove C++ dependencies that aren't needed for testing
    When I first wrote the CMakeFile, I pulled in Python and SWIG. Python
    was there because we needed its headers to drop and acquire the GIL from
    C++, but I later removed that need by making SWIG handle the GIL. SWIG
    was there because I thought we might eventually use CMake to build the
    path planner from setup.py. This turned out to be more trouble than it's
    worth.
2019-01-10 add Travis CI config and formatting script
2019-01-11 Drop Circle-CI in favor of Travis-CI. (#160)
    Removing CIrcle-CI config.
2019-01-13 Apply Probe Z offset to G30
    G30 previously took the X and Y probe offsets into account when
    probing a given position. This allow getting bed information for
    where the hotend should be instead of measuring at an offset
    position.
    This takes the Z offset into account when returning the probe
    information. This also removes the offset from being indirectly
2019-01-14 PRU queue isn't full by time if it's shutting down
    Fixes #166
2019-01-14 preserve uint64_t times in the PRU's block accounting (#168)
    Fixes #165
2019-01-15 Cleanup Journal Entries from Printing A File
2019-01-16 Update test code for G30 and G33
    The G30 and G33 commands have been updated in their handling of
    the probe offset_z config parameter. This updates the test code
    to test the changes.
2019-01-21 Add M73 stub implementation
    Adds a stub implementation for M73 P<percent>
    Stub used to prevent delays caused when M73 is in the gcode.
2019-01-25 Revert "Add M73 stub implementation"
    This reverts commit 4c7219e56fc1899c1aa820c4fc47a1607bf33806.
2019-01-27 Fix incorrect function call and add warning log
    Fixed to use the proper function call ( set_answer ).
    Adds logging message.
2019-01-31 Apply Probe Z offset to G30 (#169)
    * Apply Probe Z offset to G30
    G30 previously took the X and Y probe offsets into account when
    probing a given position. This allow getting bed information for
    where the hotend should be instead of measuring at an offset
    position.
    This takes the Z offset into account when returning the probe
2019-03-01 Address Issue 181 : Failing to set current on A4A boards
    Umikaze 2.2.1-RC2 includes updated versions of Adafruit-BBIO
    This new library changes how the SPI module works.
    This changes the DAC class to match the updated SPI module
    to use /dev/spidev2_0
2019-03-09 add stop event for Heater to wait on
    This makes heater shutdown nearly instantaneous.
2019-03-21 SPI refactor WIP
2019-03-24 revolve WIP
2019-03-31 This is the MainThread
    Obviously, this thread is still running.
    So we don’t report it.
2019-04-02 Fix M909 (set microstepping) and M92 (set steps per mm)
    - remove Printer.steps_pr_meter because it's redundant with Stepper.microsteps
    - remove callback from Stepper to Printer to update steps_pr_meter
    - remove redundant microstepping bounds check from M909 - the Steppers can do this themselves
    - add microstepping bounds check to B-series Steppers to match the A-series
    - update steps per mm in M92 correctly (instead of restarting the path planner, which doesn't help)
    - add tests for M909 and M92
2019-04-02 Cannot use “queue” as both module and local variable
2019-04-04 Fix typo in README
2019-04-04 Drop support for building `apt-get` module
    If someone wants to resurrect them, the files can recover
    the files from the previous commit
2019-04-04 To conform to 2.2.1RC
2019-04-05 Fix enough Python 3 compat issues to enable dual testing
    With this change, the tests are passing in python 2 and 3 and Travis is
    now configured to run both. A few highlights from the compat fixes:
    - fix python3 import of ConfigParser
    - fix StringIO vs io.StringIO (they were backwards)
    - switch between ConfigParser.readfp and ConfigParser.read_file
    depending on version
2019-04-05 Repair Imports
2019-04-05 Suppress traceback when resolve is called twice
2019-04-11 Improved automatic version generation
2019-04-11 Provide workaround for printer losing its position
    If G28 is issued immediately after G29 changes the
    bed compensation and saves it, the printer thinks messes up the position if a homing operation follows.
    Adding a motion allows the printer to regain the proper notion of its position
2019-04-27 Typo in series1.cfg
    Found by Andrew Rutter
2019-04-30 Revert M19 change of stepper class
    The current testing of many functions is done
    within the context of an instance of the
    complete application (Redeem).
    When this is generated, objects related to the
    hardware are constructed on the basis of the
    actual hardware found.
2019-04-30 More
2019-05-01 Python3 compatibility
    async is a reserved word
2019-05-06 Report Python Version in M115
2019-06-13 Storing key in the printer object.
2019-06-13 Added support for sending Voltage and current measured on the board
2019-07-18 Adding version and update entry points similar to toggle
2019-08-02 Fix spurious comments
2019-08-24 Bump sshpk from 1.13.1 to 1.16.1 in /docs
    Bumps [sshpk](https://github.com/joyent/node-sshpk) from 1.13.1 to 1.16.1.
    - [Release notes](https://github.com/joyent/node-sshpk/releases)
    - [Commits](https://github.com/joyent/node-sshpk/compare/v1.13.1...v1.16.1)
2019-08-24 Bump extend from 3.0.1 to 3.0.2 in /docs
    Bumps [extend](https://github.com/justmoon/node-extend) from 3.0.1 to 3.0.2.
    - [Release notes](https://github.com/justmoon/node-extend/releases)
    - [Changelog](https://github.com/justmoon/node-extend/blob/master/CHANGELOG.md)
    - [Commits](https://github.com/justmoon/node-extend/compare/v3.0.1...v3.0.2)
2020-12-29 Fix mistyped IP-address for beaglebone
2021-08-10 Bump path-parse from 1.0.5 to 1.0.7 in /docs
    Bumps [path-parse](https://github.com/jbgutierrez/path-parse) from 1.0.5 to 1.0.7.
    - [Release notes](https://github.com/jbgutierrez/path-parse/releases)
    - [Commits](https://github.com/jbgutierrez/path-parse/commits/v1.0.7)
    ---
    updated-dependencies:
    - dependency-name: path-parse

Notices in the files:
parts and their libraries:
con-headers-jp: Copyright (C) 2008, Bob Starr
